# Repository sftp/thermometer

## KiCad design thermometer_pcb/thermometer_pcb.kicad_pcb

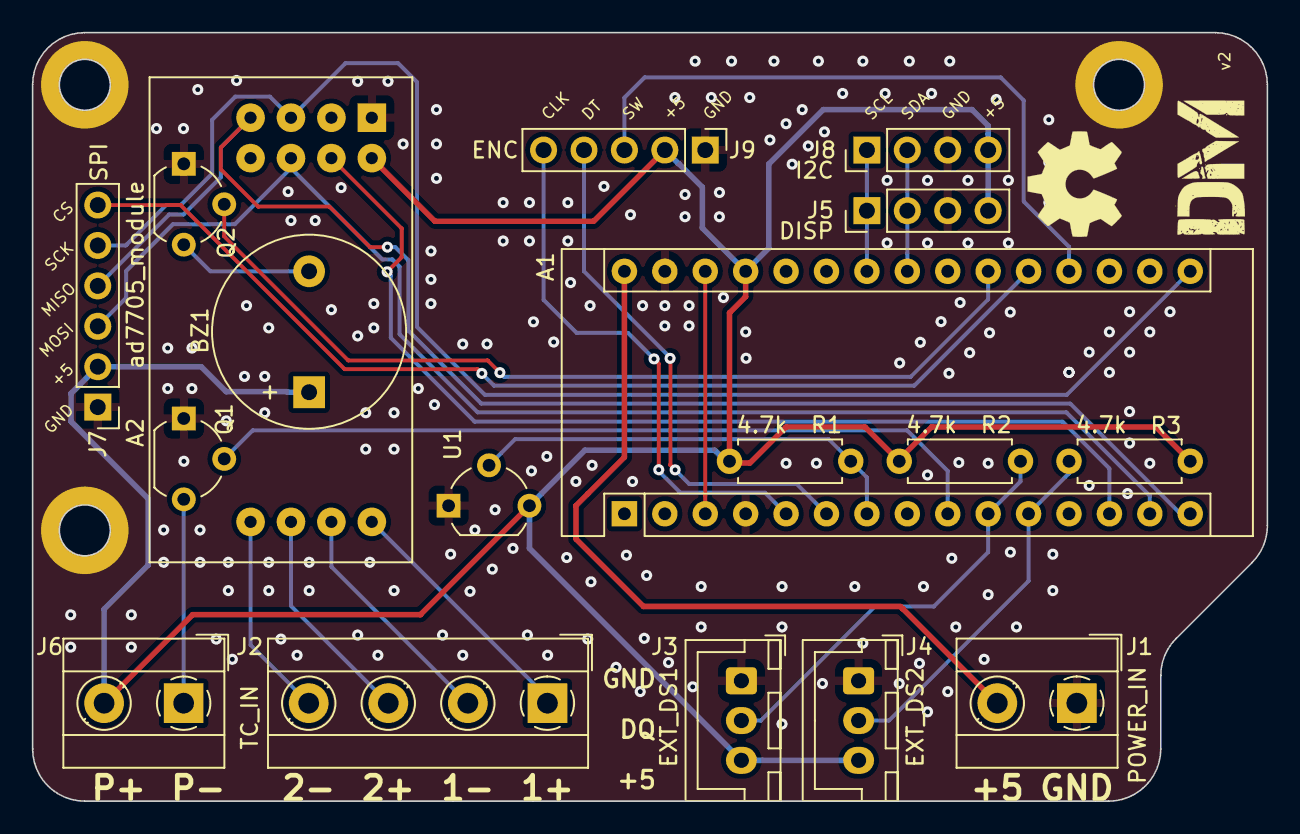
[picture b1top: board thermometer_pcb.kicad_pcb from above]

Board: 2 copper layers, 77.6 x 48.3 mm, 23 parts (0 on the bottom side), 25 nets.

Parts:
A1: Arduino_Nano_v3.x; Arduino_Nano
A2: ad7705_module
BZ1: Buzzer; Buzzer_12x9.5RM7.6
H1, H2, H3: MountingHole_Pad; MountingHole_3.2mm_M3_ISO14580_Pad
J1: POWER_IN; TerminalBlock_MetzConnect_Type055_RT01502HDWU_1x02_P5.00mm_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
J2: TC_IN; TerminalBlock_MetzConnect_Type055_RT01504HDWU_1x04_P5.00mm_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
J3: EXT_DS1; JST_XH_B3B-XH-A_1x03_P2.50mm_Vertical
J4: EXT_DS2; JST_XH_B3B-XH-A_1x03_P2.50mm_Vertical
J5: DISP; PinHeader_1x04_P2.54mm_Vertical
J6: Conn_01x02; TerminalBlock_MetzConnect_Type055_RT01502HDWU_1x02_P5.00mm_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
J7: SPI; PinHeader_1x06_P2.54mm_Vertical
J8: I2C; PinHeader_1x04_P2.54mm_Vertical
J9: ENC; PinHeader_1x05_P2.54mm_Vertical
LOGO1: Logo_Open_Hardware_Small; OSHW-Symbol_6.7x6mm_SilkScreen
Q1, Q2: PN2222A; TO-92_Wide
R1, R2, R3: 4.7k; R_Axial_DIN0207_L6.3mm_D2.5mm_P7.62mm_Horizontal
SYM1: dm_logo
U1: DS18B20; TO-92_Wide

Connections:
+5V: A1.27, A2.2, BZ1.1, J3.3, J4.3, J5.4, J6.2, J7.2, J8.4, J9.2, R1.1, R2.1, R3.1, U1.3
/2: A1.5, J9.5
/3(**): A1.6, J9.4
/4: A1.7, R1.2, U1.2
/6(**): A1.9, Q1.2
/7: A1.10, J3.2, R2.2
/8: A1.11, J4.2, R3.2
/10(**/SS): A1.13, A2.4
/11(**/MOSI): A1.14, A2.6, J7.3
/12(MISO): A1.15, A2.7, J7.4
/13(SCK): A1.16, A2.5, J7.5
/A0: A1.19, J9.3
/A1: A1.20, J7.6
/A2: A1.21, Q2.2
/A4: A1.23, J5.2, J8.2
/A5: A1.24, J5.1, J8.1
/AIN1+: A2.9, J2.1
/AIN1-: A2.10, J2.2
/AIN2+: A2.11, J2.3
/AIN2-: A2.12, J2.4
/PID_OUT-: J6.1, Q1.3
/Reset: A1.3, A1.28
/Vin: A1.30, J1.2
GND: A1.4, A1.29, A2.1, H1.1, H2.1, H3.1, J1.1, J3.1, J4.1, J5.3, J7.1, J8.3, J9.1, Q1.1, Q2.1, U1.1
unnamed: BZ1.2, Q2.3

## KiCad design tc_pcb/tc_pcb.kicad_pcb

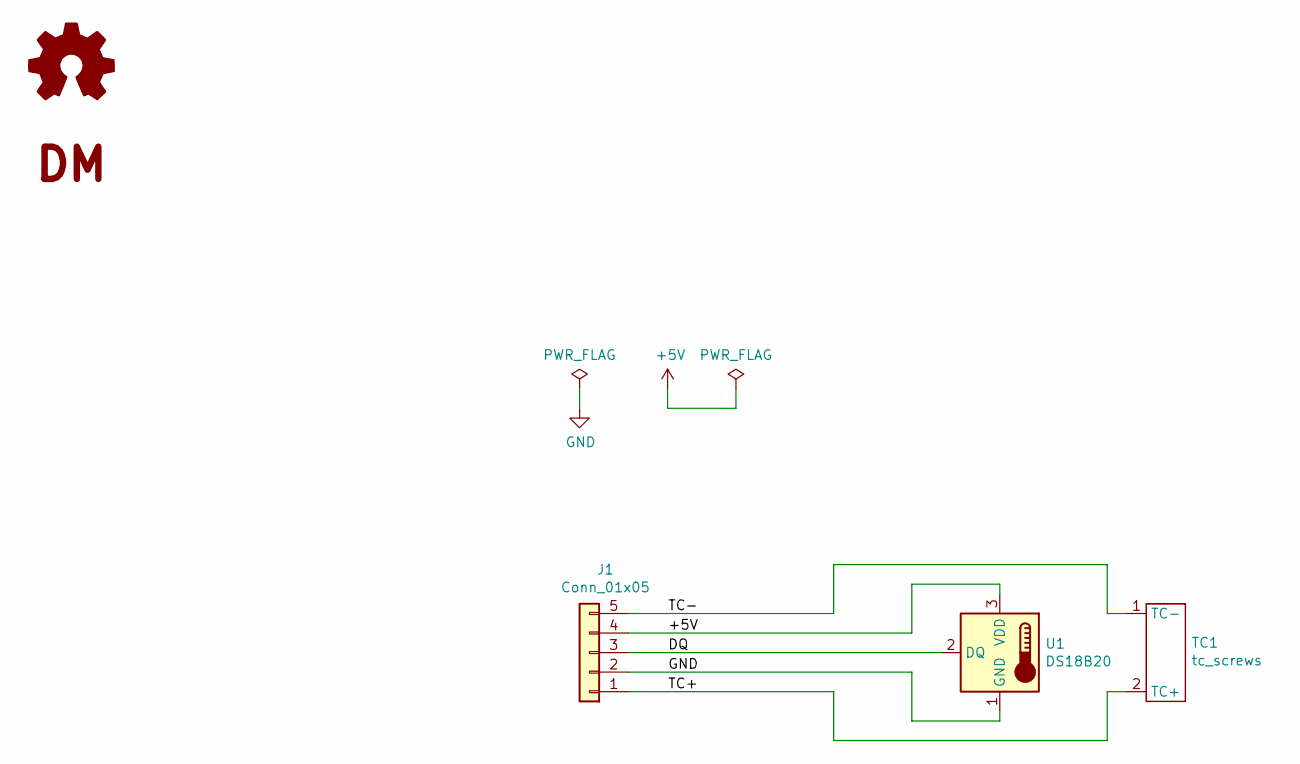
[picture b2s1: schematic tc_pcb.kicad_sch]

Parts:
J1: Conn_01x05; PinSocket_1x05_P2.54mm_Vertical
LOGO1: Logo_Open_Hardware_Small; OSHW-Symbol_6.7x6mm_SilkScreen
SYM1: dm_logo
TC1: tc_screws
U1: DS18B20; TO-92_W4.0mm_StaggerEven_Horizontal_FlatSideDown

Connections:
+5V: J1.4, U1.3 (VDD)
/DQ: J1.3, U1.2 (DQ)
/TC+: J1.1, TC1.2 (TC+)
/TC-: J1.5, TC1.1 (TC-)
GND: J1.2, U1.1 (GND)

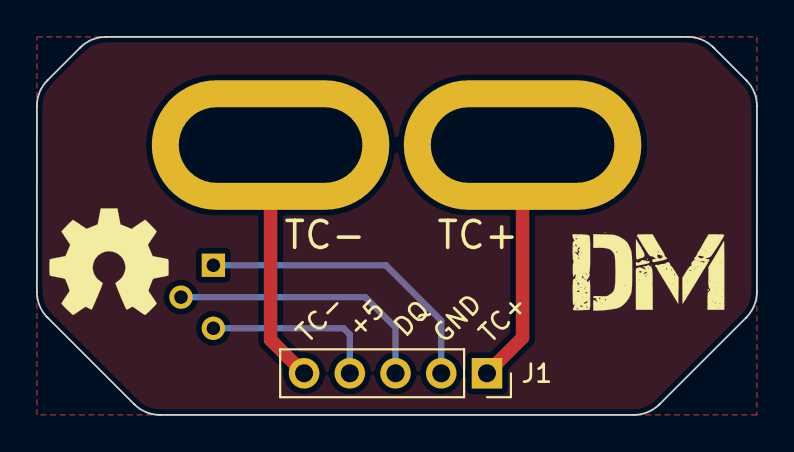
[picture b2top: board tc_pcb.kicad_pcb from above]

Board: 2 copper layers, 40.0 x 21.0 mm, 5 parts (1 on the bottom side), 5 nets.

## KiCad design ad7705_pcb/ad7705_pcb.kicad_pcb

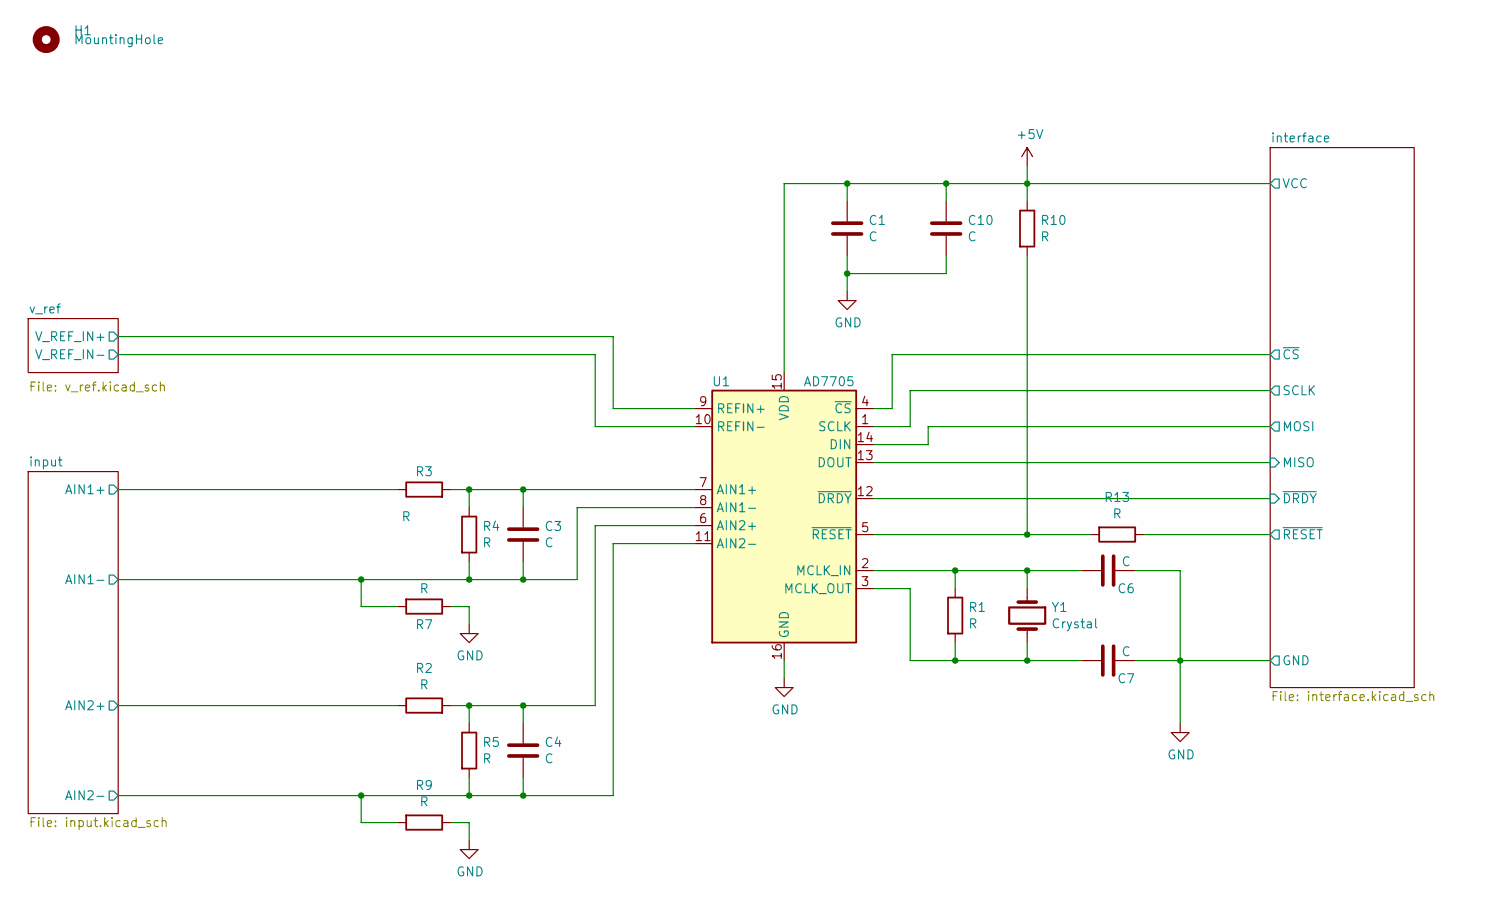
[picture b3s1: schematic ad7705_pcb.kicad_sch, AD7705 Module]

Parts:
C1, C3, C4, C6, C7, C10: C; C_0603_1608Metric
H1: MountingHole; MountingHole_2.2mm_M2_ISO7380
R1, R2, R3, R4, R5, R7, R9, R10, R13: R; R_0603_1608Metric
U1: AD7705; SOIC-16_4.55x10.3mm_P1.27mm
Y1: Crystal; Crystal_HC49-4H_Vertical

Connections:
+5V: C1.1, C10.1, R10.1, U1.15 (VDD); also elsewhere on the board
/AIN1+: R3.1; also elsewhere on the board
/AIN1-: C3.1, R4.2, R7.2, U1.8 (AIN1-); also elsewhere on the board
/AIN2+: R2.1; also elsewhere on the board
/AIN2-: C4.1, R5.2, R9.2, U1.11 (AIN2-); also elsewhere on the board
/MISO: U1.13 (DOUT); also elsewhere on the board
/MOSI: U1.14 (DIN); also elsewhere on the board
/SCLK: U1.1 (SCLK); also elsewhere on the board
/V_REF_IN+: U1.9 (REFIN+); also elsewhere on the board
/V_REF_IN-: U1.10 (REFIN-); also elsewhere on the board
/~CS: U1.4 (~CS); also elsewhere on the board
/~DRDY: U1.12 (~DRDY); also elsewhere on the board
/~RESET: R13.1; also elsewhere on the board
GND: C1.2, C6.1, C7.1, C10.2, R7.1, R9.1, U1.16 (GND); also elsewhere on the board
unnamed: C3.2, R3.2, R4.1, U1.7 (AIN1+)
unnamed: C4.2, R2.2, R5.1, U1.6 (AIN2+)
unnamed: C6.2, R1.1, U1.2 (MCLK_IN), Y1.1
unnamed: C7.2, R1.2, U1.3 (MCLK_OUT), Y1.2
unnamed: R10.2, R13.2, U1.5 (~RESET)

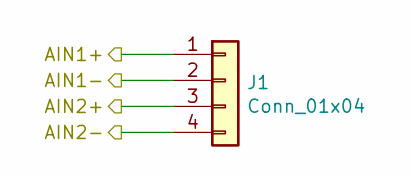
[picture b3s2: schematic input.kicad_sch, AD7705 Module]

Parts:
J1: Conn_01x04; PinHeader_1x04_P2.54mm_Vertical

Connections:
/AIN1+: J1.1; also elsewhere on the board
/AIN1-: J1.2; also elsewhere on the board
/AIN2+: J1.3; also elsewhere on the board
/AIN2-: J1.4; also elsewhere on the board

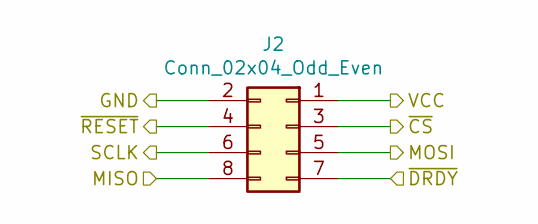
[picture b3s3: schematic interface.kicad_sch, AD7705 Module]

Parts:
J2: Conn_02x04_Odd_Even; PinHeader_2x04_P2.54mm_Vertical

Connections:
+5V: J2.1; also elsewhere on the board
/MISO: J2.8; also elsewhere on the board
/MOSI: J2.5; also elsewhere on the board
/SCLK: J2.6; also elsewhere on the board
/~CS: J2.3; also elsewhere on the board
/~DRDY: J2.7; also elsewhere on the board
/~RESET: J2.4; also elsewhere on the board
GND: J2.2; also elsewhere on the board

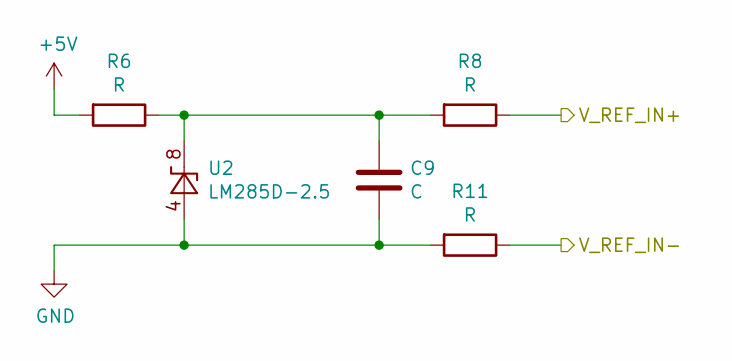
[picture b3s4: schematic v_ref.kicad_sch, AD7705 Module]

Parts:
C9: C; C_0603_1608Metric
R6, R8, R11: R; R_0603_1608Metric
U2: LM285D-2.5; SOIC-8_3.9x4.9mm_P1.27mm

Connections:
+5V: R6.2; also elsewhere on the board
/V_REF_IN+: R8.1; also elsewhere on the board
/V_REF_IN-: R11.1; also elsewhere on the board
GND: C9.2, R11.2, U2.4 (A); also elsewhere on the board
unnamed: C9.1, R6.1, R8.2, U2.8 (K)

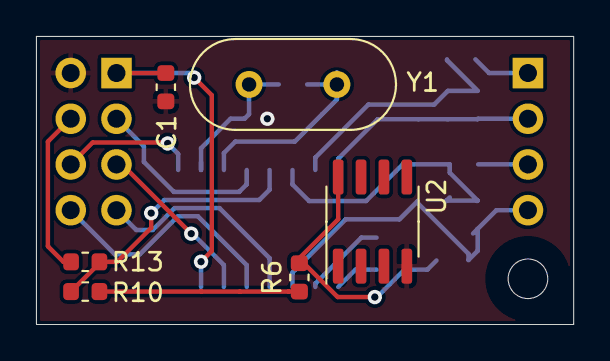
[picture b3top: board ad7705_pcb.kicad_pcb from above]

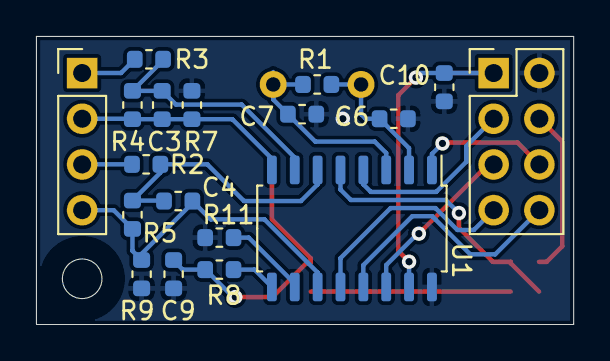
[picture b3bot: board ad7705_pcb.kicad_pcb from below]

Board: 2 copper layers, 29.8 x 16.0 mm, 25 parts (18 on the bottom side), 20 nets.

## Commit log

2017-06-24 init
2017-07-03 add wxmaxima source file
2017-07-04 fix tnn polynomial, regenerate table
2017-07-04 wxmaxima: switch from wxmx to plaintext wxm format
2017-07-04 use generated and defined table size instead of hardcoded one
2017-07-04 change type of find_t() to uint16_t
2017-07-04 add support of cold junction compensation
    Use ds18b20 sensor for to compensate cold junction temperature. Sensor
    should be mounted near with cold junction of thermocouple to measute
    reference temperature.
2017-07-08 wxmaxima/tnn: move t_max definition to top
2017-07-08 wxmaxima/tnn: use t_max value when plot ADC(t) graph
2017-07-08 wxmaxima/tnn: plot characteristic function graph
2017-07-08 wxmaxima/tnn: move t_max definition to top again
2017-07-08 use linear interpolation to calculate temperature
    This allows to save memory by reducing TNN table to 1 degree
    resolution, then calculate temperature using interpolation.
2017-07-09 calculate interpolation in other manner
    This saves 234 bytes of instructions.
2018-02-04 gitignore: add *.diff and *.patch
2018-02-04 move settings to config.h file
2018-02-04 wxmaxima: use table size constant instead of value
2018-02-04 remove display_nodate array
2018-05-06 add initial support of S-type thermocouple
2018-05-13 S-type: add full characteristic function
2018-12-31 support to output negative values
2018-12-31 config.h: change display pins (prepare for pcb)
2019-01-01 config.h: change ds18b20 pin (prepare for pcb)
2019-01-01 move delay value definition to config.h
2019-02-03 mv tc-specific gain definition from config
2019-02-03 rename generated tc files
2019-02-17 tc.h: fix type in S-type include
2019-07-01 new tc tables: use t(ADC) tables
    Using t(ADC) tables allows to lookup t in one step (O(1)), no need to
    bisect in ADC(t) table.
2019-07-01 remove old tc tables
2019-07-01 add support of K-type tc
2019-07-01 wxmaxima/tc_n.wxm: use t_max var instead of magic number
2019-07-02 add support of external ds18b20 cold junction compensation sensor
    If connected, external sensor will be used for cold junction compensation.
    Otherwise, fallback to internal sensor.
2019-07-02 multiply ds18b20 temp by 10 before cast to int
2019-07-03 ds18b20: use int functions instead of float
    This saves 480 bytes.
2019-07-04 ds18b20: do not wait for conversion
    Use timer (millis()) to ensure conversion is done.
2019-07-04 setup(): fix indentation
2019-07-04 ds18b20: allow to set resolution
2019-07-04 config: move DS18B20_DELAY_MS to ds18b20 section
2019-07-04 pcb: add initial pcb
2019-07-05 pcb: add gitignore for thermometer_pcb
2019-07-05 thermometer_pcb/gitignore: ignore gerber files
2019-07-05 thermometer_pcb/gitignore: ignore drill files
2019-07-05 thermometer_pcb/gitignore: ignore .kicad_pcb-bak
2019-07-05 pcb: add7705_module: flip to another side
2019-07-05 pcb: add7705_module footprint: remove B.Silk
2019-07-05 pcb: update add7705_module footprint from lib
2019-07-05 pcb: fix J2 connector pads order
2019-07-07 pcb: change connectors for ds18b20 sensors
2019-07-07 prepare new pcb shape
2019-07-07 pcb: minor cleanups
2019-07-08 pcb: minor traces shape improvement
2019-07-08 pcb: add micro vias
2019-07-08 pcb: add more via stitching
2019-07-08 pcb: add silkscreen text for conns
2019-07-08 pcb: drc cleanups
2019-07-15 pcb: add pid connector
2019-07-15 pcb: remove wrong micro-via
2019-07-15 pcb: move logos
2019-07-15 pcb: move transistor nearer to conn
2019-07-25 get rid of delay() call
    Use millis() timer value to determine if task need to be executed.
2019-07-25 move neg flag to display task
2019-07-25 update ms when task was executed
2019-07-26 add task executing debug
2019-07-26 increase serial baudrate 9600->115200
2019-08-04 pcb: move conns and it's silkscreen
2019-08-04 pcb: add pid conn silkscreen
2019-08-04 pcb: move J6 silkscreen
2019-08-04 pcb: move TC conn silkscreen
2019-08-04 pcb: reroute PID+ track
2019-08-04 pcb: make +5V track shorter
2019-08-17 pcb: reroute all nets; move resistors
2019-08-17 pcb: add SPI pinheader
2019-08-17 pcb: add buzzer
2019-08-17 pcb: add I2C pinheader
2019-08-17 pcb: add SPI pins silkscreen
2019-08-17 pcb: rotate Q1 silkscreen
2019-08-17 pcb: add I2C pins silkscreen
2019-08-17 pcb: move R{1,2,3} silkscreen
2019-08-17 pcb: change DS18 pins
2019-08-17 pcb: add encoder pinheader
2019-08-17 pcb: fix tracks shape
2019-08-17 pcb: add microvias
2019-08-17 pcb: add microvia
2019-08-17 pcb: fix track shape
2019-08-17 pcb: swap layers
2019-08-17 pcb: add version to silkscreen
2019-08-18 gitignore: add *.zip
2019-08-18 pcb: big via for +5v
2019-08-21 thermometer_pcb/gitignore: ignore *.{csv,html,xml}
2019-08-26 gitignore: move pcb ignores to root gitignore
2019-08-26 pcb: add thermocouple pcb
2019-09-08 gitignore: ignore *.dsn
2019-09-08 pcb: use A0 for encoders switch
2019-09-08 gitignore: ignore *.sch-bak
2019-09-08 pcb: use A1 for external SPI CS
2019-09-08 pcb: use A2 for buzzer
2019-09-08 pcb: move some tracks to back layer
2019-09-08 pcb: version v2
2019-09-08 pcb: align some tracks
2019-09-08 pcb: remove wrong track segment
2019-09-08 pcb: get rid of via on Vin track
2019-09-08 pcb: align J{1,2,3,4,6} Silk label
2019-09-22 add initial support of PID control with encoder setup
2019-09-22 move ad7705 vref definition to config
2019-09-22 pid: fix conservative params applying
2019-09-28 pid: write setpoint to eeprom
2019-09-28 tasks: use uint32_t for ms (millis since start) variable
2019-09-29 pid: tune P and I
2019-09-30 encoder: configure direction with config
2019-09-30 encoder: set direction to -1 by default
2019-10-05 recalc t after adc read
2019-10-05 move display data preparation and output to its own func
2019-10-05 move display initialization to its own func
2019-10-05 add forgotten ms update
2019-10-05 place ms updates before tasks starts
2019-10-05 fix ms used in debug output
2019-10-05 use ms variable instead of millis() call when possibple
2019-10-05 tune setpoint with integer step
2019-10-05 remove unneeded disp_val variable
2019-10-05 pid: do not use conservotive PID params by default
2019-10-05 move find_t() to tc.h
2020-01-08 menu: add basic screen-based menu
2020-01-08 gitignore: ignore pcb rescue files
2020-01-08 gitignore: ignore pcb's sym-lib-table
2020-07-22 add ad7705_module kicad project
2020-07-22 ad7705_pcb: fix silk
2020-07-22 gitignore: ignore *.kicad_prl
2020-07-22 thermometer_pcb: move to new kicad
2020-07-22 tc_pcb: move to new kicad
2020-07-22 kicad-lib: tc_screws: new file format
2020-07-22 kicad-lib: AD7705: new file format
2020-07-22 kicad-lib: ad7705_module: new file format
2020-07-22 kicad-lib: dm_logo: new file format
2020-07-26 pcb: tune corners radius
2020-07-26 pcb: move some traces
2020-07-26 pcb: use nicro-via for CLK and DT encoder lines
2020-07-26 pcb: use micro-via for SS, MISO, A1, A2 lines
2020-07-26 tc_pcb: remove redundand labels
2020-07-26 gitignore: ignore generated pdf files
2020-07-26 tc_pcb: set dimensions in mils
2020-10-15 pcb: change dimensions
2020-10-15 gitignore: ignore pcb's dxf files
2020-10-15 gitignore: ignore kicad autosave files
2020-10-15 pcb: remove dimensions on copper layer
2024-02-26 move to kicad 8
